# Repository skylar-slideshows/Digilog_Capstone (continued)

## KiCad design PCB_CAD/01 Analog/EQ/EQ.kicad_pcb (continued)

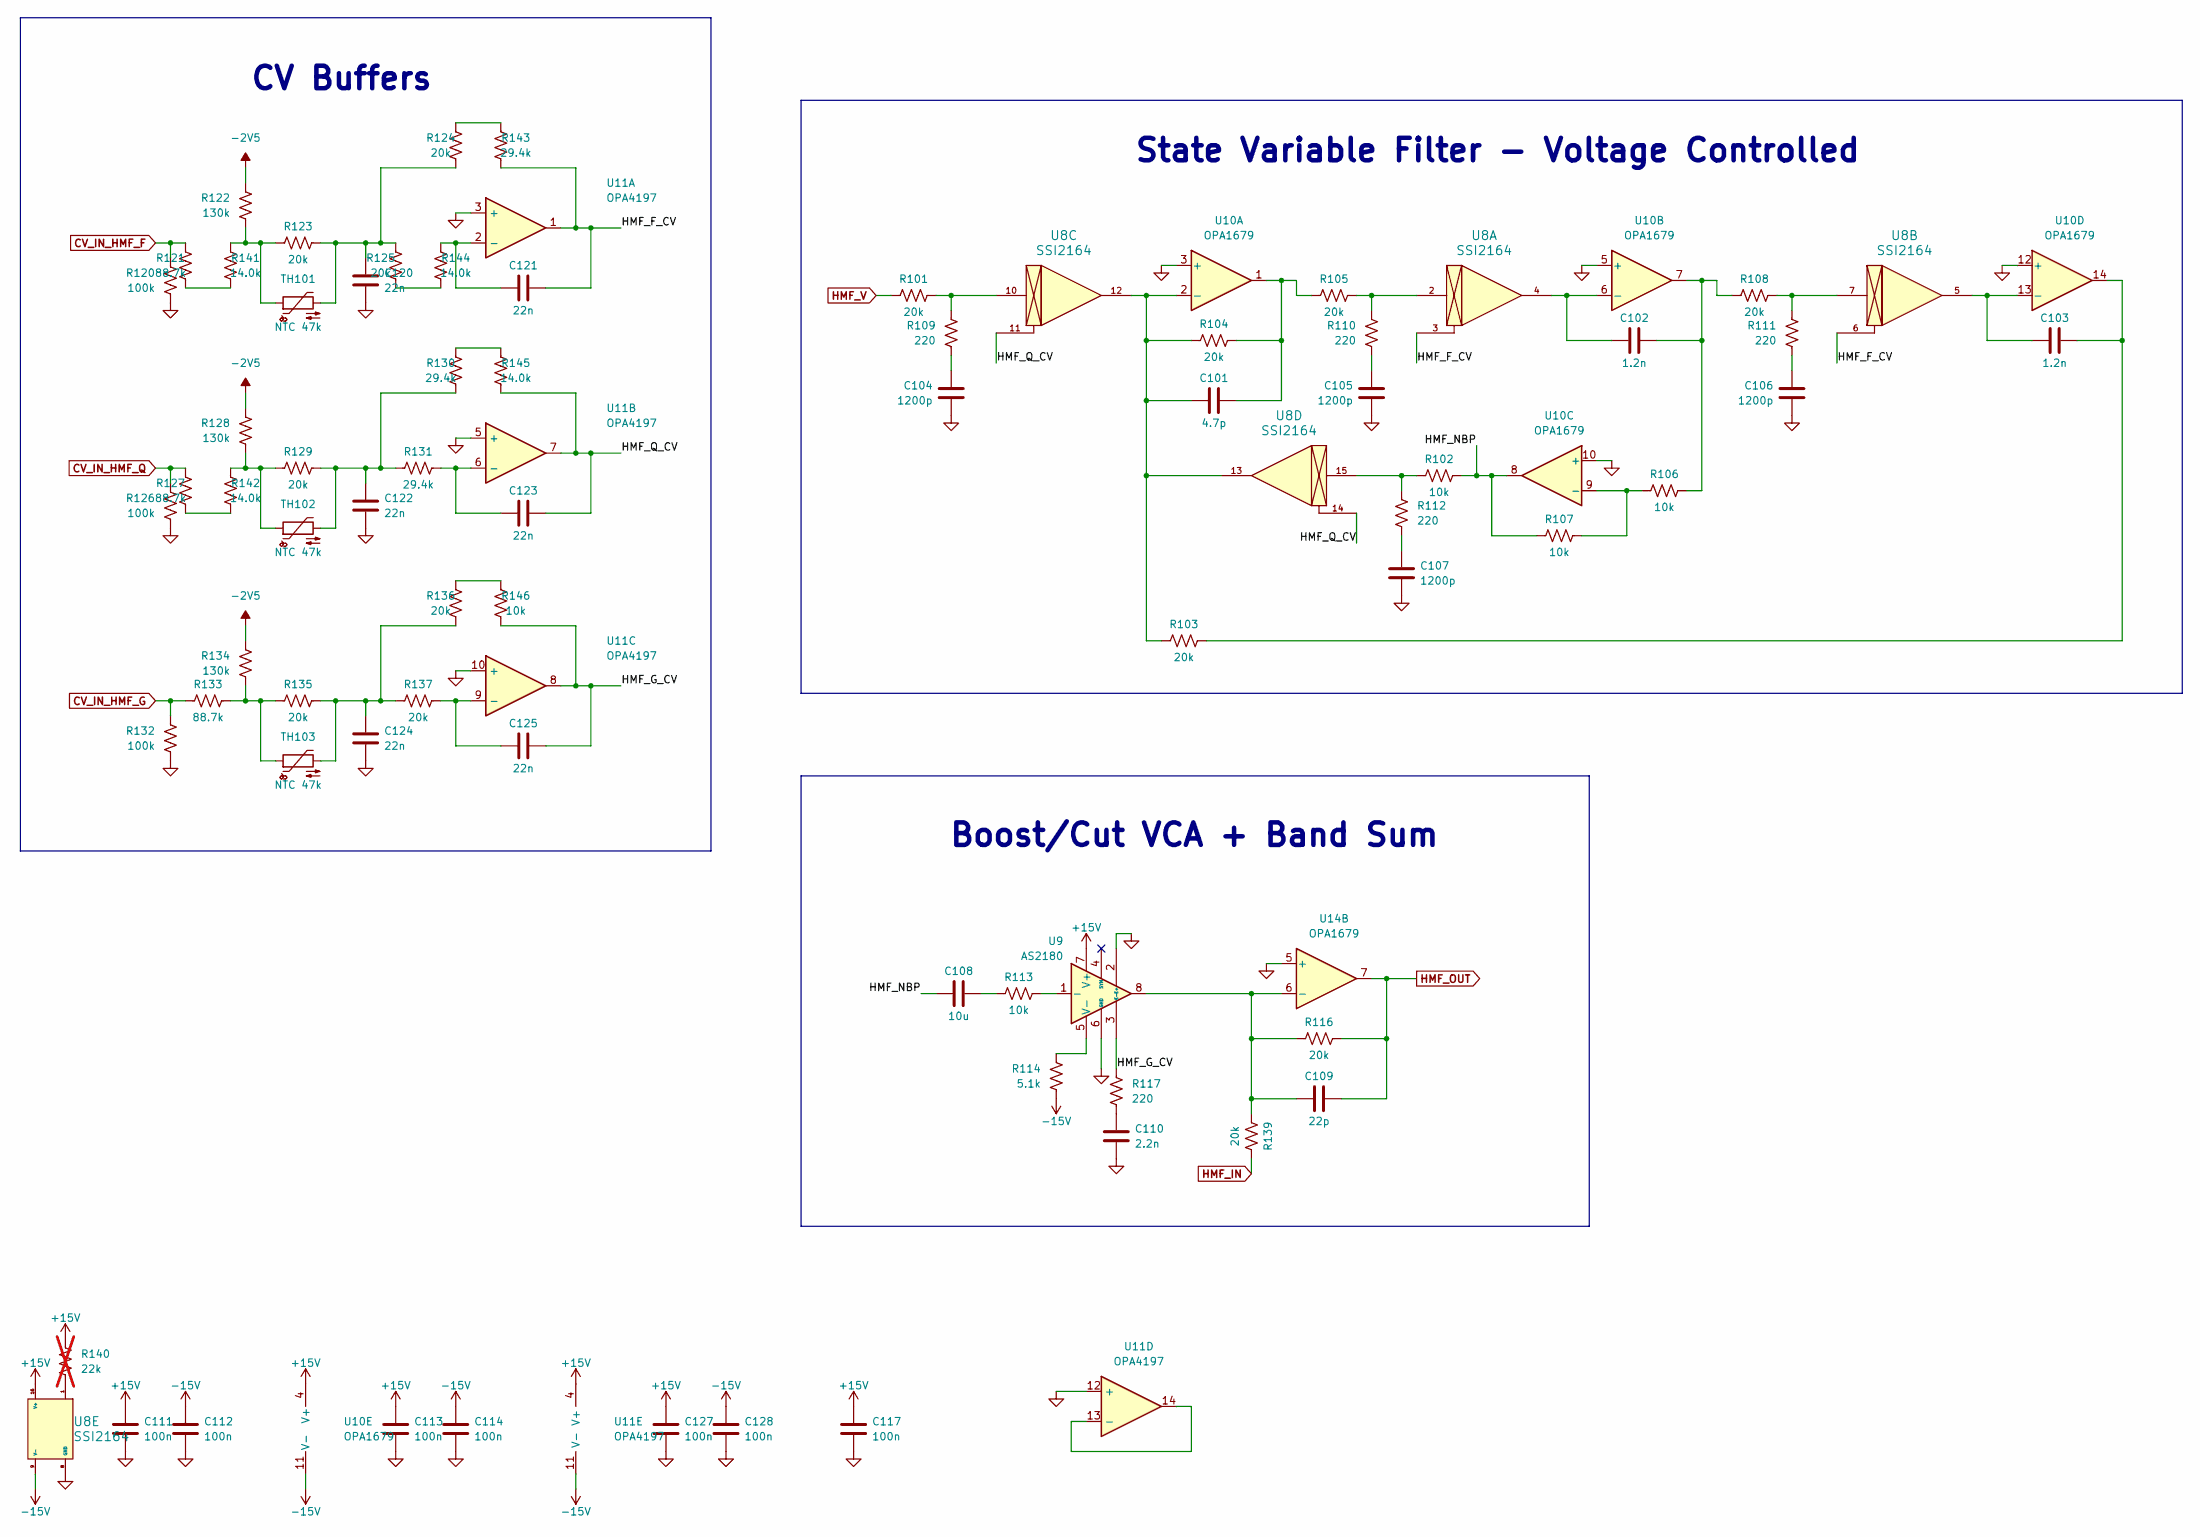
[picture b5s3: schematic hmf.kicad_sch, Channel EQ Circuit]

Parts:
C101: 4.7p; C_0603_1608Metric; LCSC C282071
C102, C103: 1.2n; C_1206_3216Metric; LCSC C527278
C104, C105, C106, C107: 1200p; C_1206_3216Metric; LCSC C527278
C108: 10u; CP_Elec_6.3x5.4_Nichicon; LCSC C340735
C109: 22p; C_0603_1608Metric; LCSC C105620
C110: 2.2n; C_0805_2012Metric; LCSC C107103
C111, C112, C113, C114, C117, C127, C128: 100n; C_0603_1608Metric; LCSC C1591
C120, C121, C122, C123, C124, C125: 22n; C_1206_3216Metric; LCSC C7500389
R101, R103, R104, R105, R108, R116, R123, R124, R125, R129, R135, R136, R137, R139: 20k; R_0603_1608Metric; LCSC C311888
R102, R106, R107, R113, R146: 10k; R_0603_1608Metric; LCSC C95204
R109, R110, R111, R112, R117: 220; R_0603_1608Metric; LCSC C318124
R114: 5.1k; R_0603_1608Metric; LCSC C122969
R120, R126, R132: 100k; R_0603_1608Metric; LCSC C122538
R121, R127, R133: 88.7k; R_0603_1608Metric; LCSC C728599
R122, R128, R134: 130k; R_0603_1608Metric; LCSC C473257
R130, R131, R143: 29.4k; R_0603_1608Metric; LCSC C667085
R140: 22k; R_0603_1608Metric; LCSC C335085; not fitted
R141, R142, R144, R145: 14.0k; R_0603_1608Metric; LCSC C705941
TH101, TH102, TH103: NTC 47k; R_Axial_DIN0207_L6.3mm_D2.5mm_P2.54mm_Vertical; MPN NTCLE100E3473JB0; LCSC dnp
U8: SSI2164; SSI2164_breakout; LCSC dnp
U9: AS2180; PinHeader_1x08_P2.54mm_Vertical; LCSC dnp
U10, U14: OPA1679; SOIC-14_3.9x8.7mm_P1.27mm; LCSC C2878631
U11: OPA4197; SOIC-14_3.9x8.7mm_P1.27mm; LCSC C2058532

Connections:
+15V: C111.1, C113.1, C117.1, C127.1, R140.1, U8.16 (V+), U9.7 (V+), U10.4 (V+), U11.4 (V+); also elsewhere on the board
-2V5: R122.1, R128.1, R134.1; also elsewhere on the board
-15V: C112.1, C114.1, C128.1, R114.2, U8.9 (V-), U10.11 (V-), U11.11 (V-); also elsewhere on the board
/HMF/HMF_F_CV: C121.2, R143.2, U8.3, U8.6, U11.1
/HMF/HMF_G_CV: C125.2, R117.1, R146.2, U9.3 (E-), U11.8
/HMF/HMF_NBP: C108.1, R102.2, R107.1, U10.8
/HMF/HMF_Q_CV: C123.2, R145.2, U8.11, U8.14, U11.7
CV_IN_HMF_F: R120.1, R121.1; also elsewhere on the board
CV_IN_HMF_G: R132.1, R133.1; also elsewhere on the board
CV_IN_HMF_Q: R126.1, R127.1; also elsewhere on the board
GND: C104.2, C105.2, C106.2, C107.2, C110.2, C111.2, C112.2, C113.2, C114.2, C117.2, C120.2, C122.2, C124.2, C127.2, C128.2, R120.2, R126.2, R132.2, U8.8 (GND), U9.2 (E+), U9.6 (GND), U10.3 (+), U10.5 (+), U10.10 (+), U10.12 (+), U11.3 (+), U11.5 (+), U11.10 (+), U11.12 (+), U14.5 (+); also elsewhere on the board
HMF_IN: R139.2; also elsewhere on the board
HMF_OUT: C109.2, R116.2, U14.7; also elsewhere on the board
HMF_V: R101.1; also elsewhere on the board
unnamed: C101.2, R104.2, R105.1, U10.1
unnamed: C102.2, R106.2, R108.1, U10.7
unnamed: C103.2, R103.2, U10.14
unnamed: C104.1, R109.2
unnamed: C105.1, R110.2
unnamed: C106.1, R111.2
unnamed: C107.1, R112.2
unnamed: C108.2, R113.1
unnamed: C110.1, R117.2
unnamed: C120.1, R123.2, R124.1, R125.1, TH101.2
unnamed: C122.1, R129.2, R130.1, R131.1, TH102.2
unnamed: C124.1, R135.2, R136.1, R137.1, TH103.2
unnamed: R101.2, R109.1, U8.10
unnamed: R102.1, R112.1, U8.15
unnamed: R105.2, R110.1, U8.2
unnamed: R108.2, R111.1, U8.7
unnamed: R121.2, R141.1
unnamed: R122.2, R123.1, R141.2, TH101.1
unnamed: R124.2, R143.1
unnamed: R125.2, R144.1
unnamed: R127.2, R142.1
unnamed: R128.2, R129.1, R142.2, TH102.1
unnamed: R130.2, R145.1
unnamed: R133.2, R134.2, R135.1, TH103.1
unnamed: R136.2, R146.1
unnamed: R140.2, U8.1
unnamed: R113.2, U9.1 (-)
unnamed: R114.1, U9.5 (V-)
unnamed: C101.1, R103.1, R104.1, U8.12, U8.13, U10.2 (-)
unnamed: C102.1, U8.4, U10.6 (-)
unnamed: R106.1, R107.2, U10.9 (-)
unnamed: C103.1, U8.5, U10.13 (-)
unnamed: C121.1, R144.2, U11.2 (-)
unnamed: C123.1, R131.2, U11.6 (-)
unnamed: C125.1, R137.2, U11.9 (-)
unnamed: U11.13 (-), U11.14
unnamed: C109.1, R116.1, R139.1, U9.8, U14.6 (-)

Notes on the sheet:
State Variable Filter - Voltage Controlled
CV Buffers
Boost/Cut VCA + Band Sum

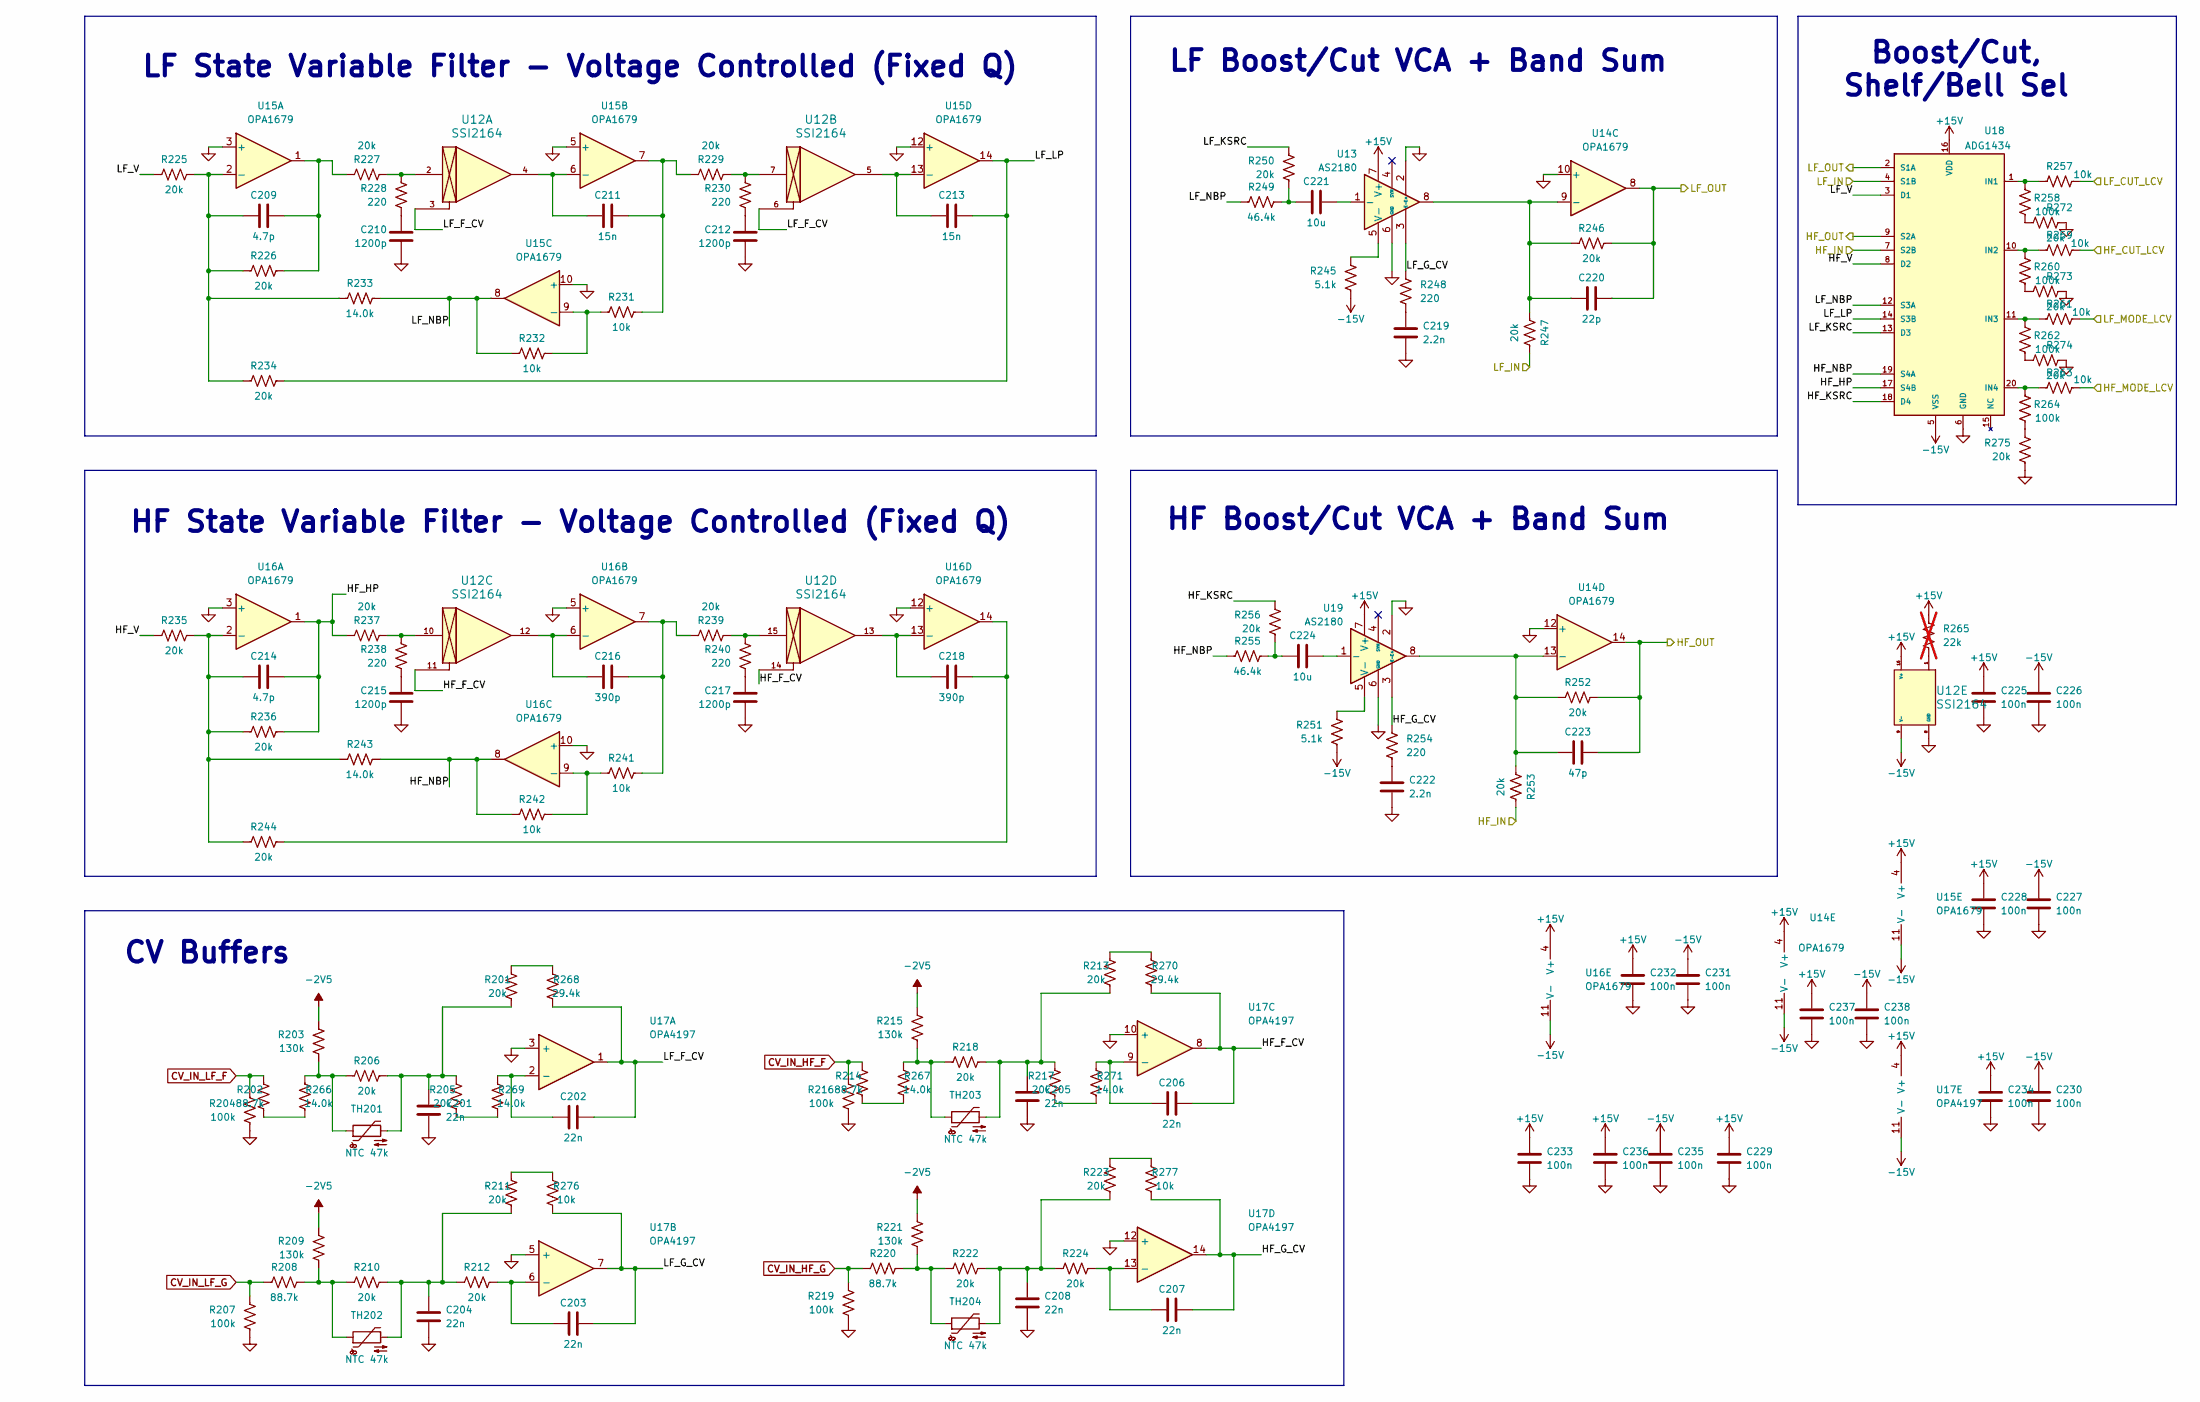
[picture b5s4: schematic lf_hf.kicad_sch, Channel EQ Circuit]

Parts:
C201, C202, C203, C204, C205, C206, C207, C208: 22n; C_1206_3216Metric; LCSC C7500389
C209, C214: 4.7p; C_0603_1608Metric; LCSC C282071
C210, C212, C215, C217: 1200p; C_1206_3216Metric; LCSC C527278
C211, C213: 15n; C_Rect_L7.2mm_W2.5mm_P5.00mm; LCSC dnp
C216, C218: 390p; C_0603_1608Metric; LCSC C107050
C219, C222: 2.2n; C_0805_2012Metric; LCSC C107103
C220: 22p; C_0603_1608Metric; LCSC C105620
C221, C224: 10u; CP_Elec_6.3x5.4_Nichicon; LCSC C340735
C223: 47p; C_0603_1608Metric; LCSC C105622
C225, C226, C227, C228, C229, C230, C231, C232, C233, C234, C235, C236, C237, C238: 100n; C_0603_1608Metric; LCSC C1591
R201, R205, R206, R210, R211, R212, R213, R217, R218, R222, R223, R224, R225, R226, R227, R229, R234, R235, R236, R237, R239, R244, R246, R247, R250, R252, R253, R256, R272, R273, R274, R275: 20k; R_0603_1608Metric; LCSC C311888
R202, R208, R214, R220: 88.7k; R_0603_1608Metric; LCSC C728599
R203, R209, R215, R221: 130k; R_0603_1608Metric; LCSC C473257
R204, R207, R216, R219, R258, R260, R262, R264: 100k; R_0603_1608Metric; LCSC C122538
R228, R230, R238, R240, R248, R254: 220; R_0603_1608Metric; LCSC C318124
R231, R232, R241, R242, R257, R259, R261, R263, R276, R277: 10k; R_0603_1608Metric; LCSC C95204
R233, R243, R266, R267, R269, R271: 14.0k; R_0603_1608Metric; LCSC C705941
R245, R251: 5.1k; R_0603_1608Metric; LCSC C122969
R249, R255: 46.4k; R_0603_1608Metric; LCSC C861420
R265: 22k; R_0603_1608Metric; LCSC C335085; not fitted
R268, R270: 29.4k; R_0603_1608Metric; LCSC C667085
TH201, TH202, TH203, TH204: NTC 47k; R_Axial_DIN0207_L6.3mm_D2.5mm_P2.54mm_Vertical; MPN NTCLE100E3473JB0; LCSC dnp
U12: SSI2164; SSI2164_breakout; LCSC dnp
U13, U19: AS2180; PinHeader_1x08_P2.54mm_Vertical; LCSC dnp
U14, U15, U16: OPA1679; SOIC-14_3.9x8.7mm_P1.27mm; LCSC C2878631
U17: OPA4197; SOIC-14_3.9x8.7mm_P1.27mm; LCSC C2058532
U18: ADG1434; TSSOP-20_4.4x6.5mm_P0.65mm; LCSC C408906

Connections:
+15V: C225.1, C228.1, C229.1, C232.1, C233.1, C234.1, C236.1, C237.1, R265.1, U12.16 (V+), U13.7 (V+), U14.4 (V+), U15.4 (V+), U16.4 (V+), U17.4 (V+), U18.16 (VDD), U19.7 (V+); also elsewhere on the board
-2V5: R203.1, R209.1, R215.1, R221.1; also elsewhere on the board
-15V: C226.1, C227.1, C230.1, C231.1, C235.1, C238.1, R245.2, R251.2, U12.9 (V-), U14.11 (V-), U15.11 (V-), U16.11 (V-), U17.11 (V-), U18.5 (VSS); also elsewhere on the board
/EQ_OUT: C223.2, R252.2, U14.14, U18.9 (S2A); also elsewhere on the board
/LF_HF/HF_CUT_LCV: R259.2; also elsewhere on the board
/LF_HF/HF_F_CV: C206.2, R270.2, U12.11, U12.14, U17.8
/LF_HF/HF_G_CV: C207.2, R254.1, R277.2, U17.14, U19.3 (E-)
/LF_HF/HF_HP: C214.2, R236.2, R237.1, U16.1, U18.17 (S4B)
/LF_HF/HF_KSRC: R256.1, U18.18 (D4)
/LF_HF/HF_MODE_LCV: R263.2; also elsewhere on the board
/LF_HF/HF_NBP: R242.1, R243.2, R255.1, U16.8, U18.19 (S4A)
/LF_HF/HF_V: R235.1, U18.8 (D2)
/LF_HF/LF_CUT_LCV: R257.2; also elsewhere on the board
/LF_HF/LF_F_CV: C202.2, R268.2, U12.3, U12.6, U17.1
/LF_HF/LF_G_CV: C203.2, R248.1, R276.2, U13.3 (E-), U17.7
/LF_HF/LF_IN: R247.2, U18.4 (S1B); also elsewhere on the board
/LF_HF/LF_KSRC: R250.1, U18.13 (D3)
/LF_HF/LF_LP: C213.2, R234.2, U15.14, U18.14 (S3B)
/LF_HF/LF_MODE_LCV: R261.2; also elsewhere on the board
/LF_HF/LF_NBP: R232.1, R233.2, R249.1, U15.8, U18.12 (S3A)
/LF_HF/LF_OUT: C220.2, R246.2, U14.8, U18.2 (S1A); also elsewhere on the board
/LF_HF/LF_V: R225.1, U18.3 (D1)
CV_IN_HF_F: R214.1, R216.1; also elsewhere on the board
CV_IN_HF_G: R219.1, R220.1; also elsewhere on the board
CV_IN_LF_F: R202.1, R204.1; also elsewhere on the board
CV_IN_LF_G: R207.1, R208.1; also elsewhere on the board
GND: C201.2, C204.2, C205.2, C208.2, C210.2, C212.2, C215.2, C217.2, C219.2, C222.2, C225.2, C226.2, C227.2, C228.2, C229.2, C230.2, C231.2, C232.2, C233.2, C234.2, C235.2, C236.2, C237.2, C238.2, R204.2, R207.2, R216.2, R219.2, R272.2, R273.2, R274.2, R275.2, U12.8 (GND), U13.2 (E+), U13.6 (GND), U14.10 (+), U14.12 (+), U15.3 (+), U15.5 (+), U15.10 (+), U15.12 (+), U16.3 (+), U16.5 (+), U16.10 (+), U16.12 (+), U17.3 (+), U17.5 (+), U17.10 (+), U17.12 (+), U18.6 (GND), U19.2 (E+), U19.6 (GND); also elsewhere on the board
HMF_OUT: R253.2, U18.7 (S2B); also elsewhere on the board
unnamed: C201.1, R201.1, R205.1, R206.2, TH201.2
unnamed: C204.1, R210.2, R211.1, R212.1, TH202.2
unnamed: C205.1, R213.1, R217.1, R218.2, TH203.2
unnamed: C208.1, R222.2, R223.1, R224.1, TH204.2
unnamed: C209.2, R226.2, R227.1, U15.1
unnamed: C210.1, R228.2
unnamed: C211.2, R229.1, R231.2, U15.7
unnamed: C212.1, R230.2
unnamed: C215.1, R238.2
unnamed: C216.2, R239.1, R241.2, U16.7
unnamed: C217.1, R240.2
unnamed: C218.2, R244.2, U16.14
unnamed: C219.1, R248.2
unnamed: C221.1, R249.2, R250.2
unnamed: C222.1, R254.2
unnamed: C224.1, R255.2, R256.2
unnamed: R201.2, R268.1
unnamed: R202.2, R266.1
unnamed: R203.2, R206.1, R266.2, TH201.1
unnamed: R205.2, R269.1
unnamed: R208.2, R209.2, R210.1, TH202.1
unnamed: R211.2, R276.1
unnamed: R213.2, R270.1
unnamed: R214.2, R267.1
unnamed: R215.2, R218.1, R267.2, TH203.1
unnamed: R217.2, R271.1
unnamed: R220.2, R221.2, R222.1, TH204.1
unnamed: R223.2, R277.1
unnamed: R227.2, R228.1, U12.2
unnamed: R229.2, R230.1, U12.7
unnamed: R237.2, R238.1, U12.10
unnamed: R239.2, R240.1, U12.15
unnamed: R258.2, R272.1
unnamed: R260.2, R273.1
unnamed: R262.2, R274.1
unnamed: R264.2, R275.1
unnamed: R265.2, U12.1
unnamed: C221.2, U13.1 (-)
unnamed: R245.1, U13.5 (V-)
unnamed: C220.1, R246.1, R247.1, U13.8, U14.9 (-)
unnamed: C223.1, R252.1, R253.1, U14.13 (-), U19.8
unnamed: C209.1, R225.2, R226.1, R233.1, R234.1, U15.2 (-)
unnamed: C211.1, U12.4, U15.6 (-)
unnamed: R231.1, R232.2, U15.9 (-)
unnamed: C213.1, U12.5, U15.13 (-)
unnamed: C214.1, R235.2, R236.1, R243.1, R244.1, U16.2 (-)
unnamed: C216.1, U12.12, U16.6 (-)
unnamed: R241.1, R242.2, U16.9 (-)
unnamed: C218.1, U12.13, U16.13 (-)
unnamed: C202.1, R269.2, U17.2 (-)
unnamed: C203.1, R212.2, U17.6 (-)
unnamed: C206.1, R271.2, U17.9 (-)
unnamed: C207.1, R224.2, U17.13 (-)
unnamed: R257.1, R258.1, U18.1 (IN1)
unnamed: R259.1, R260.1, U18.10 (IN2)
unnamed: R261.1, R262.1, U18.11 (IN3)
unnamed: R263.1, R264.1, U18.20 (IN4)
unnamed: C224.2, U19.1 (-)
unnamed: R251.1, U19.5 (V-)

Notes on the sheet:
LF Boost/Cut VCA + Band Sum
LF State Variable Filter - Voltage Controlled (Fixed Q)
HF Boost/Cut VCA + Band Sum
HF State Variable Filter - Voltage Controlled (Fixed Q)
Boost/Cut, Shelf/Bell Sel
CV Buffers

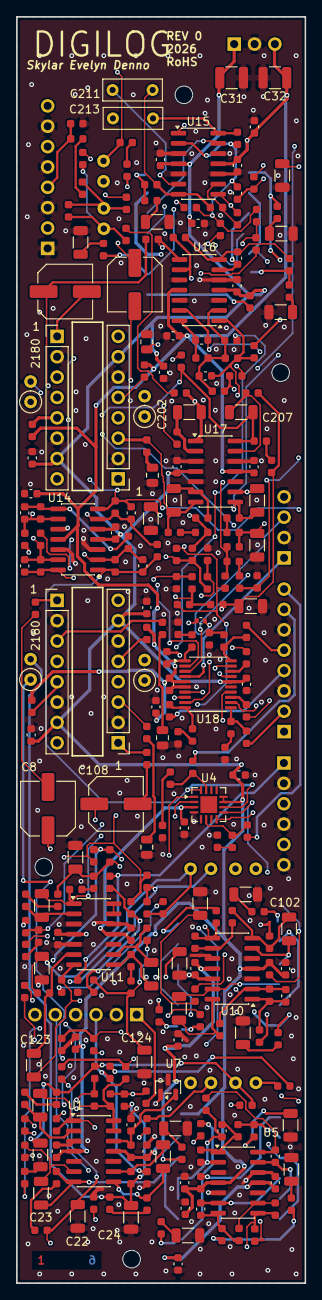
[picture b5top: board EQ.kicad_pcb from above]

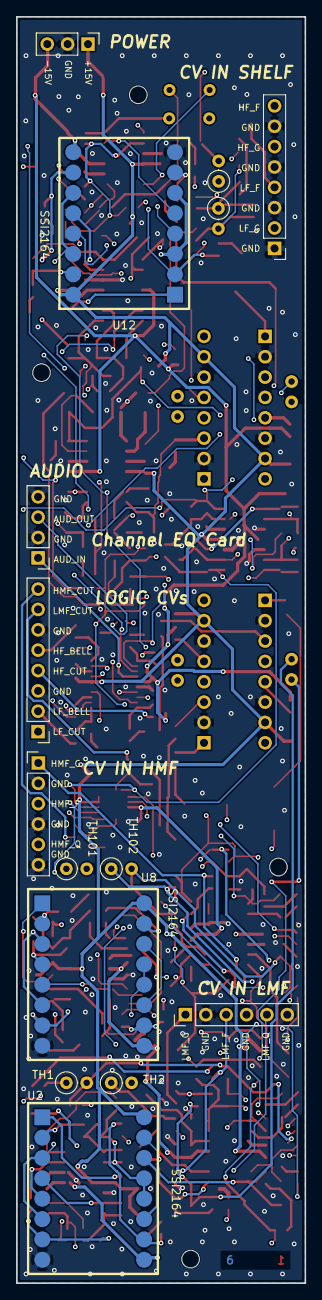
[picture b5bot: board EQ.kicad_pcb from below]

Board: 6 copper layers, 36.0 x 158.0 mm, 297 parts (15 on the bottom side), 185 nets.

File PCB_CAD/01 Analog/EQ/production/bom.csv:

Designator,Footprint,Quantity,Value,LCSC Part #
"C1, C101, C209, C214",0603,4,4.7p,C282071
"C10, C110, C219, C222",0805,4,2.2n,C107103
"C102, C103",1206,2,1.2n,C527278
"C104, C105, C106, C107, C210, C212, C215, C217, C4, C5, C6, C7",1206,12,1200p,C527278
"C108, C221, C224, C8",CP_Elec_6.3x5.4_Nichicon,4,10u,C340735
"C109, C220, C9",0603,3,22p,C105620
"C11, C111, C112, C113, C114, C117, C12, C127, C128, C13, C14, C17, C18, C19, C225, C226, C227, C228, C229, C230, C231, C232, C233, C234, C235, C236, C237, C238, C27, C28, C29",0603,31,100n,C1591
"C120, C121, C122, C123, C124, C125, C20, C201, C202, C203, C204, C205, C206, C207, C208, C21, C22, C23, C24, C25",1206,20,22n,C7500389
"C2, C3",0603,2,3.3n,C107048
"C211, C213",C_Rect_L7.2mm_W2.5mm_P5.00mm,2,15n,dnp
"C216, C218",0603,2,390p,C107050
C223,0603,1,47p,C105622
C26,0603,1,100n,C1590
"C31, C32",1210,2,22u 25V,C21397
J1,PinHeader_1x04_P2.54mm_Vertical,1,AUDIO,dnp
J2,PinHeader_1x08_P2.54mm_Vertical,1,LF_HF_CV,dnp
J3,PinHeader_1x08_P2.54mm_Vertical,1,LOGIC_CV,dnp
J4,PinHeader_1x03_P2.54mm_Vertical,1,POWER,dnp
J5,PinHeader_1x06_P2.54mm_Vertical,1,HMF_CV,dnp
J6,PinHeader_1x06_P2.54mm_Vertical,1,LMF_CV,dnp
"R1, R101, R103, R104, R105, R108, R116, R123, R124, R125, R129, R135, R136, R137, R139, R16, R201, R205, R206, R210, R211, R212, R213, R217, R218, R222, R223, R224, R225, R226, R227, R229, R23, R234, R235, R236, R237, R239, R24, R244, R246, R247, R25, R250, R252, R253, R256, R272, R273, R274, R275, R29, R3, R35, R36, R37, R39, R4, R47, R48, R5, R8",0603,62,20k,C311888
"R10, R109, R11, R110, R111, R112, R117, R12, R17, R228, R230, R238, R240, R248, R254, R9",0603,16,220,C318124
"R102, R106, R107, R113, R13, R146, R18, R2, R231, R232, R241, R242, R257, R259, R261, R263, R276, R277, R40, R50, R6, R7",0603,22,10k,C95204
"R114, R14, R245, R251",0603,4,5.1k,C122969
"R120, R126, R132, R19, R20, R204, R207, R216, R219, R258, R26, R260, R262, R264, R32, R41",0603,16,100k,C122538
"R121, R127, R133, R202, R208, R21, R214, R220, R27, R33",0603,10,88.7k,C728599
"R122, R128, R134, R203, R209, R215, R22, R221, R28, R34",0603,10,130k,C473257
"R130, R131, R143, R268, R270, R30, R31, R45",0603,8,29.4k,C667085
"R140, R265, R42",0603,3,22k,C335085
"R141, R142, R144, R145, R233, R243, R266, R267, R269, R271, R43, R44, R46, R49",0603,14,14.0k,C705941
R15,0402,1,100,C317909
"R249, R255, R38",0603,3,46.4k,C861420
"TH1, TH101, TH102, TH103, TH2, TH201, TH202, TH203, TH204, TH3",R_Axial_DIN0207_L6.3mm_D2.5mm_P2.54mm_Vertical,10,NTC 47k,dnp
"U1, U11, U17",SOIC-14_3.9x8.7mm_P1.27mm,3,OPA4197,C2058532
"U10, U14, U15, U16, U5",SOIC-14_3.9x8.7mm_P1.27mm,5,OPA1679,C2057264
"U12, U2, U8",SSI2164_breakout,3,SSI2164,dnp
"U13, U19, U3, U9",PinHeader_1x08_P2.54mm_Vertical,4,AS2180,dnp
U18,TSSOP-20_4.4x6.5mm_P0.65mm,1,ADG1434,C408906
U4,Analog_LFCSP-16-1EP_4x4mm_P0.65mm_EP2.1x2.1mm,1,ADG1436,C655227
U7,SOT-23,1,ADR5041,C659596

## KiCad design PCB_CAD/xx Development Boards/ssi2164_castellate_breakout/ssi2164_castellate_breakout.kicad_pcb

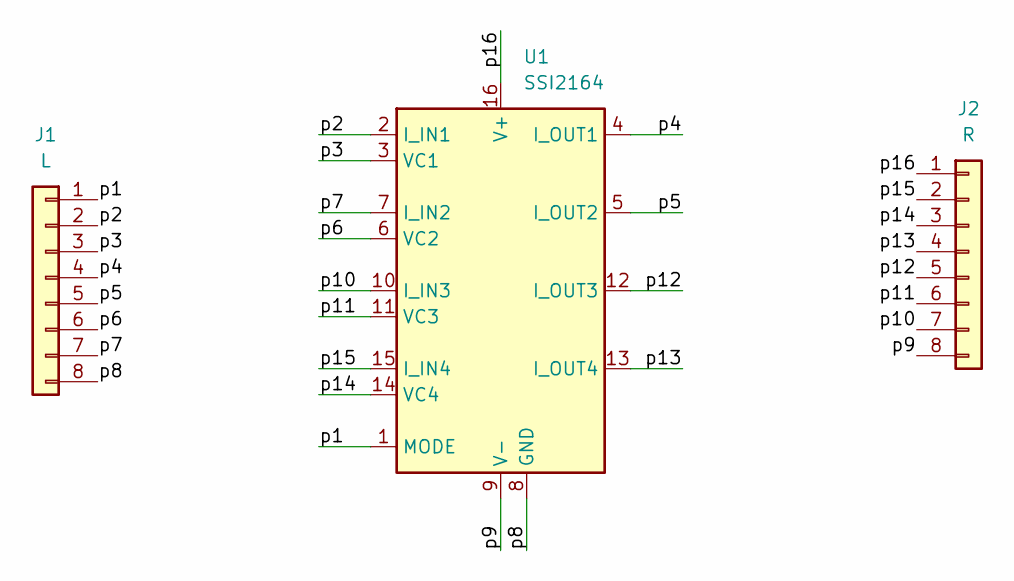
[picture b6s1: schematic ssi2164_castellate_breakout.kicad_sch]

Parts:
J1: L; PinHeader_1x08_P2.54mm_Vertical_big
J2: R; PinHeader_1x08_P2.54mm_Vertical_big
U1: SSI2164; SOIC-16_3.9x9.9mm_P1.27mm

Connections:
/p1: J1.1, U1.1 (MODE)
/p2: J1.2, U1.2 (I_IN1)
/p3: J1.3, U1.3 (VC1)
/p4: J1.4, U1.4 (I_OUT1)
/p5: J1.5, U1.5 (I_OUT2)
/p6: J1.6, U1.6 (VC2)
/p7: J1.7, U1.7 (I_IN2)
/p8: J1.8, U1.8 (GND)
/p9: J2.8, U1.9 (V-)
/p10: J2.7, U1.10 (I_IN3)
/p11: J2.6, U1.11 (VC3)
/p12: J2.5, U1.12 (I_OUT3)
/p13: J2.4, U1.13 (I_OUT4)
/p14: J2.3, U1.14 (VC4)
/p15: J2.2, U1.15 (I_IN4)
/p16: J2.1, U1.16 (V+)

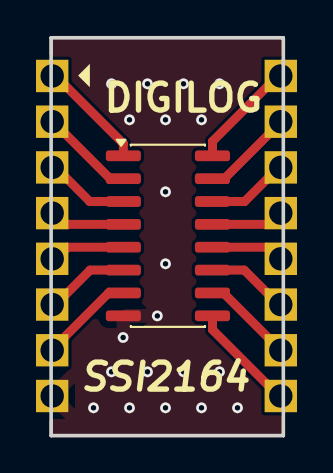
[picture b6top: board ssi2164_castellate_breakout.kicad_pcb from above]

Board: 2 copper layers, 12.9 x 22.1 mm, 3 parts (0 on the bottom side), 16 nets.

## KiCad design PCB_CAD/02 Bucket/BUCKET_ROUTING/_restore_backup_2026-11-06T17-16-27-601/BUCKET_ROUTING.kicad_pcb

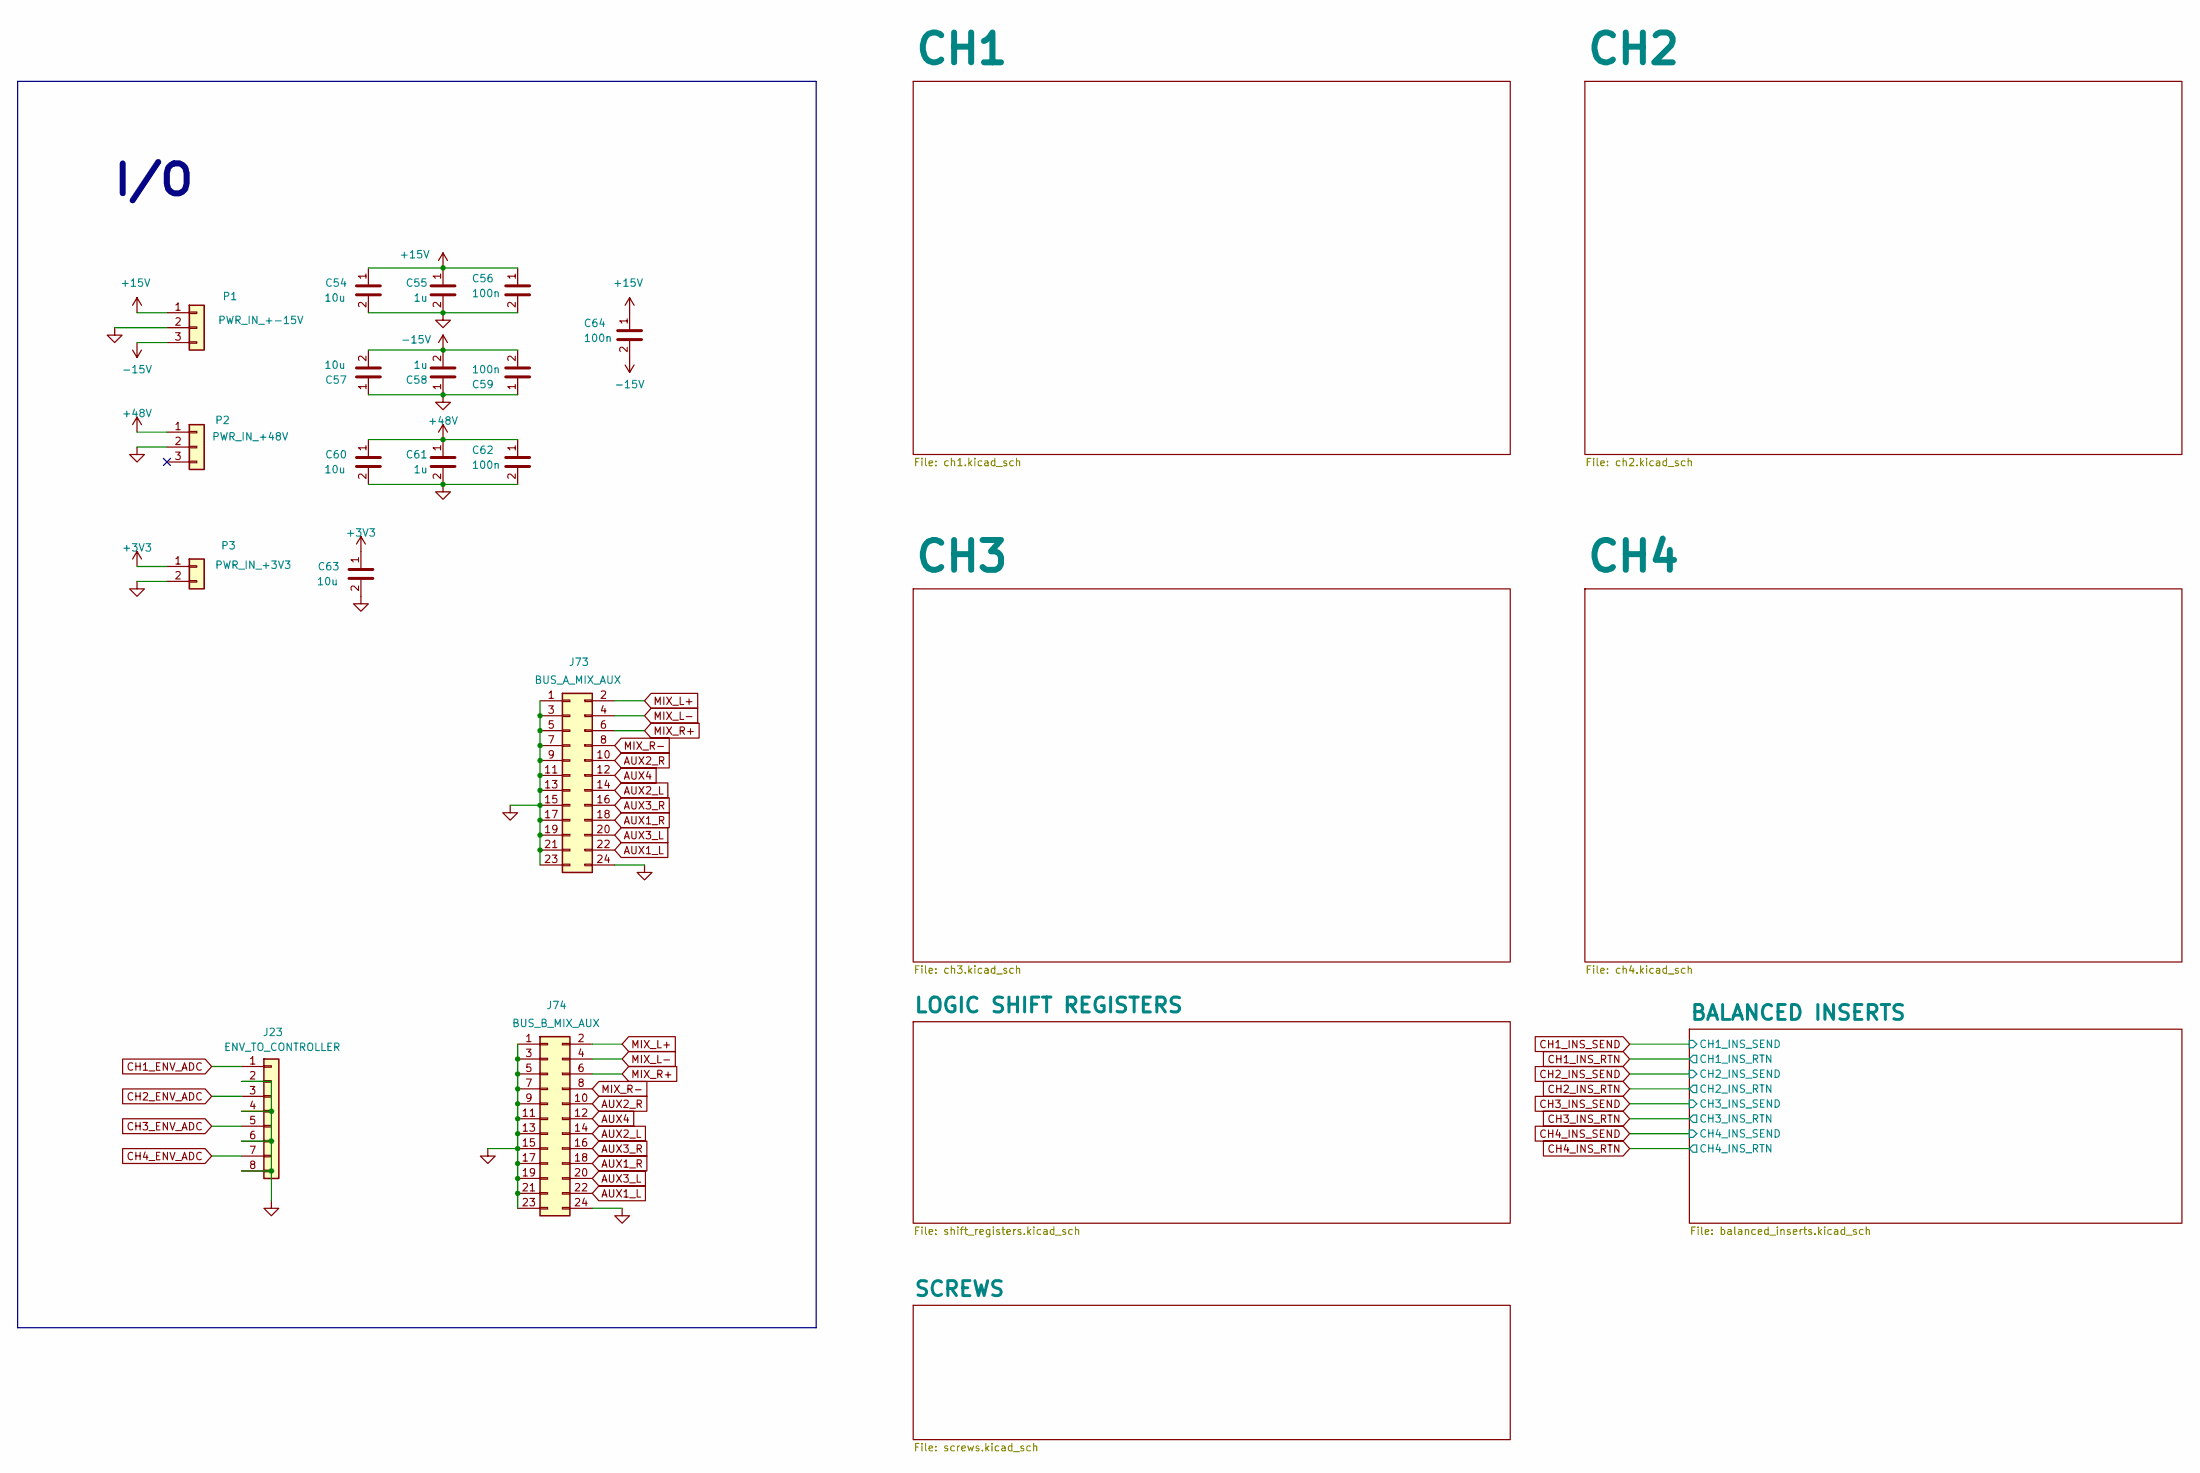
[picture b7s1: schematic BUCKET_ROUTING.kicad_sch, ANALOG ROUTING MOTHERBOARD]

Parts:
C54, C57, C60, C63: 10u; C_1206_3216Metric
C55, C58, C61: 1u; C_0603_1608Metric
C56, C59, C62, C64: 100n; C_0603_1608Metric
J23: ENV_TO_CONTROLLER; PinHeader_1x08_P2.54mm_Vertical
J73: BUS_A_MIX_AUX; IDC-Header_2x12_P2.54mm_Vertical
J74: BUS_B_MIX_AUX; IDC-Header_2x12_P2.54mm_Vertical
P1: PWR_IN_+-15V; Samtec_HPM-03-05-x-S_Straight_1x03_Pitch5.08mm
P2: PWR_IN_+48V; Samtec_HPM-03-05-x-S_Straight_1x03_Pitch5.08mm
P3: PWR_IN_+3V3; PinSocket_1x02_P2.54mm_Vertical

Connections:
+3V3: C63.1, P3.1; also elsewhere on the board
+15V: C54.1, C55.1, C56.1, C64.1, P1.1; also elsewhere on the board
+48V: C60.1, C61.1, C62.1, P2.1; also elsewhere on the board
-15V: C57.2, C58.2, C59.2, C64.2, P1.3; also elsewhere on the board
AUX1_L: J73.22, J74.22; also elsewhere on the board
AUX1_R: J73.18, J74.18; also elsewhere on the board
AUX2_L: J73.14, J74.14; also elsewhere on the board
AUX2_R: J73.10, J74.10; also elsewhere on the board
AUX3_L: J73.20, J74.20; also elsewhere on the board
AUX3_R: J73.16, J74.16; also elsewhere on the board
AUX4: J73.12, J74.12; also elsewhere on the board
CH1_ENV_ADC: J23.1; also elsewhere on the board
CH2_ENV_ADC: J23.3; also elsewhere on the board
CH3_ENV_ADC: J23.5; also elsewhere on the board
CH4_ENV_ADC: J23.7; also elsewhere on the board
GND: C54.2, C55.2, C56.2, C57.1, C58.1, C59.1, C60.2, C61.2, C62.2, C63.2, J23.2, J23.4, J23.6, J23.8, J73.1, J73.3, J73.5, J73.7, J73.9, J73.11, J73.13, J73.15, J73.17, J73.19, J73.21, J73.23, J73.24, J74.1, J74.3, J74.5, J74.7, J74.9, J74.11, J74.13, J74.15, J74.17, J74.19, J74.21, J74.23, J74.24, P1.2, P2.2, P3.2; also elsewhere on the board
MIX_L+: J73.2, J74.2; also elsewhere on the board
MIX_L-: J73.4, J74.4; also elsewhere on the board
MIX_R+: J73.6, J74.6; also elsewhere on the board
MIX_R-: J73.8, J74.8; also elsewhere on the board

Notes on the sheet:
I/O
